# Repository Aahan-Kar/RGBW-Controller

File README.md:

# RGBW LED Strip Controller

Welcome to the repository for the RGBW LED Strip Controller! This project is designed for enthusiasts and professionals looking to control non-addressable RGBW LED strips with precision and flexibility. Using a Teensy 3.2 microcontroller, this controller offers high-frequency PWM for smooth LED dimming, compatibility with both RGB and single-color strips, and both manual and software control options.

## Features

- **High-Frequency PWM**: The controller operates at a 23.4 kHz PWM frequency to minimize visible flicker, ensuring smooth light output.
- **Compatibility**: Designed for use with non-addressable RGBW LED strips, but also supports RGB and single-color (white) strips.
- **12V Input**: Supports a 12V input for LED driving and internal electronics, ensuring wide compatibility with common LED strip specifications.
- **Power Control**: Includes a power on/off switch for easy power management.
- **Manual Control**: Features four knobs for adjusting the brightness levels of the Red, Green, Blue, and White channels independently.
- **USB Connectivity**: Offers USB connectivity for software control, making it suitable for integration with computer-managed setups like 3D printers with Raspberry Pi controllers.
- **Mode Selection**: A rocker switch allows for easy toggling between manual (hardware) control and software control modes.

## Repository Contents

- `Eagle/` - Contains Eagle CAD files including both the electronic schematics and PCB layout designs in a single directory, as preferred by Eagle CAD.
- `Gerber/` - Gerber files ready for PCB fabrication.
- `Code/` - Source code for the Teensy 3.2 microcontroller, including the PWM control and USB communication logic.
- `3DCAD/` - 3D CAD files for the controller's enclosure, suitable for 3D printing.

## Getting Started

### Hardware Setup

1. **Power Supply Connection**: Connect a 12V power supply to the barrel connector. Ensure your power supply can handle the current draw of your LED setup.
2. **Power On**: Use the power switch to turn on the controller.
3. **LED Strip Connection**: Connect your RGBW, RGB, or White LED strip to the appropriate terminals on the controller.

### Manual Control

- With the mode selector switched to hardware control, use the knobs on the controller to adjust the brightness levels of each channel to your liking.

### Software Control

- Ensure the mode selector is set to software control.
- Connect the controller to your computer via USB. It should be recognized as a serial (RS232) device.
- You can now send commands from your computer to adjust the LED strip's settings. This is particularly useful for automated setups like lighting effects for 3D printers.

## Contributing

Contributions to this project are welcome! Whether it's bug fixes, feature enhancements, or documentation improvements, please feel free to fork the repository and submit a pull request.

## License

This project is released under the [MIT License](LICENSE.md). Feel free to use, modify, and distribute the code and designs as per the license terms.

## Contact

For questions, suggestions, or to report issues, please open an issue in this repository, and we'll get back to you as soon as possible.

Happy Lighting!

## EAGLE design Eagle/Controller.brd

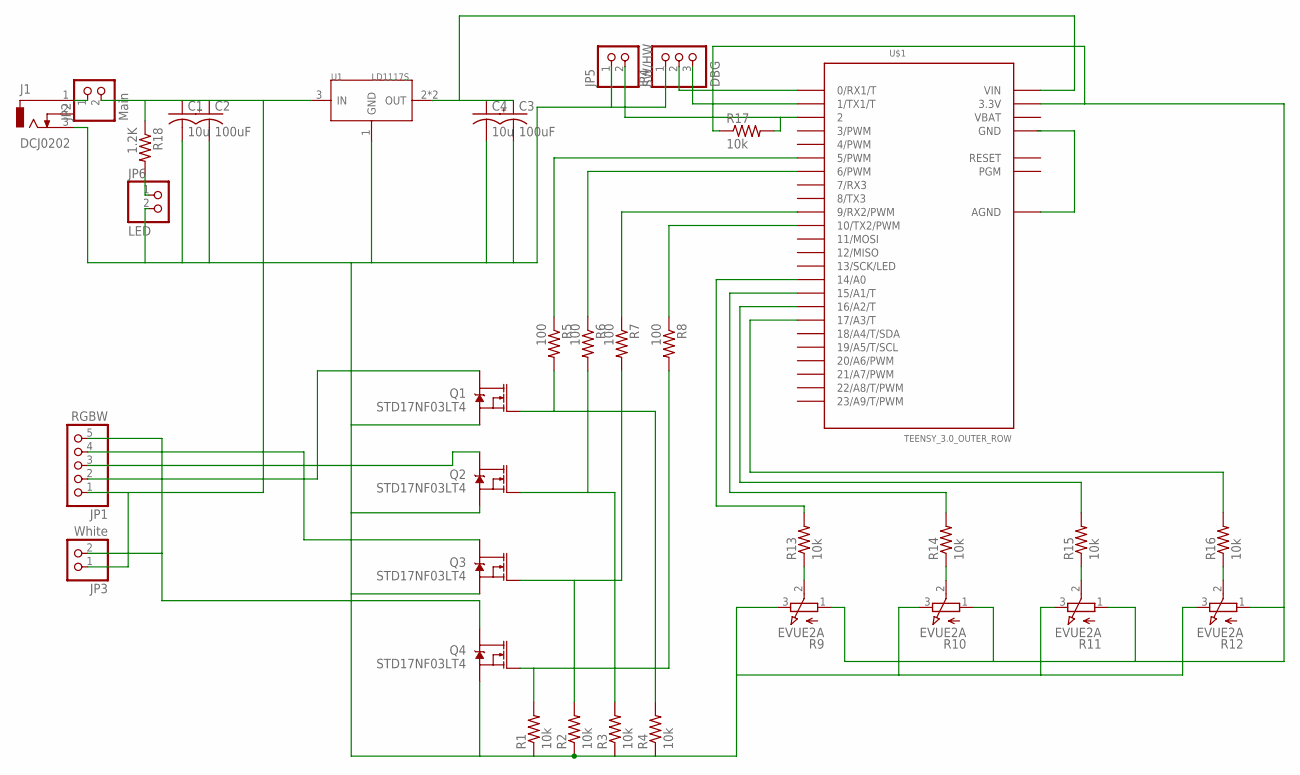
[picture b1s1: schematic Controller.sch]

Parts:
C1, C4: 10u; ADAFRUIT_C0805
C2, C3: 100uF; RCL_TT2D6
J1: DCJ0202
JP1: RGBW; 1X05/90
JP2: Main; 1X02
JP3: White; 1X02/90
JP4: DBG; 1X03/90
JP5: SW/HW; 1X02
JP6: LED; 1X02
Q1, Q2, Q3, Q4: STD17NF03LT4; DPAK
R1, R2, R3, R4, R13, R14, R15, R16, R17: 10k; R0805
R5, R6, R7, R8: 100; R0805
R9, R10, R11, R12: EVUE2A; EVUE
R18: 1.2K; R0805
U1: LD1117S; SOT-223
U$1: TEENSY_3.0_OUTER_ROW; TEENSY_3.0-3.2&LC_OUTER_ROW

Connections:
GND: C1.2, C2.-, C3.-, C4.2, J1.3, JP4.1, JP5.1, JP6.2, Q1.3 (S), Q2.3 (S), Q3.3 (S), Q4.3 (S), R1.1, R2.1, R3.1, R4.1, R9.3 (E), R10.3 (E), R11.3 (E), R12.3 (E), U1.1 (GND), U$1.GND, U$1.GND1 (GND)
unnamed: C1.1, C2.+, JP1.1, JP2.2, JP3.1, R18.1, U1.3 (IN)
unnamed: C3.+, C4.1, U1.2 (OUT), U1.TER (OUT), U$1.VIN
unnamed: R5.1, U$1.5 (5/PWM)
unnamed: Q4.1 (G), R1.2, R8.2
unnamed: Q3.1 (G), R2.2, R7.2
unnamed: Q2.1 (G), R3.2, R6.2
unnamed: Q1.1 (G), R4.2, R5.2
unnamed: R6.1, U$1.6 (6/PWM)
unnamed: R7.1, U$1.9 (9/RX2/PWM)
unnamed: R8.1, U$1.10 (10/TX2/PWM)
unnamed: R9.2 (S), R13.1
unnamed: JP1.2, Q1.4 (D)
unnamed: JP1.3, Q2.4 (D)
unnamed: JP1.4, Q3.4 (D)
unnamed: JP1.5, JP3.2, Q4.4 (D)
unnamed: J1.1, JP2.1
unnamed: R10.2 (S), R14.1
unnamed: R11.2 (S), R15.1
unnamed: R12.2 (S), R16.1
unnamed: R9.1 (A), R10.1 (A), R11.1 (A), R12.1 (A), R17.1, U$1.3.3V, U$1.3.3V1 (3.3V)
unnamed: R13.2, U$1.14/A0
unnamed: R14.2, U$1.15/A1 (15/A1/T)
unnamed: R15.2, U$1.16/A2 (16/A2/T)
unnamed: R16.2, U$1.17/A3 (17/A3/T)
unnamed: JP5.2, R17.2, U$1.2
unnamed: JP4.2, U$1.0 (0/RX1/T)
unnamed: JP4.3, U$1.1 (1/TX1/T)
unnamed: JP6.1, R18.2
VBAT: U$1.VBAT

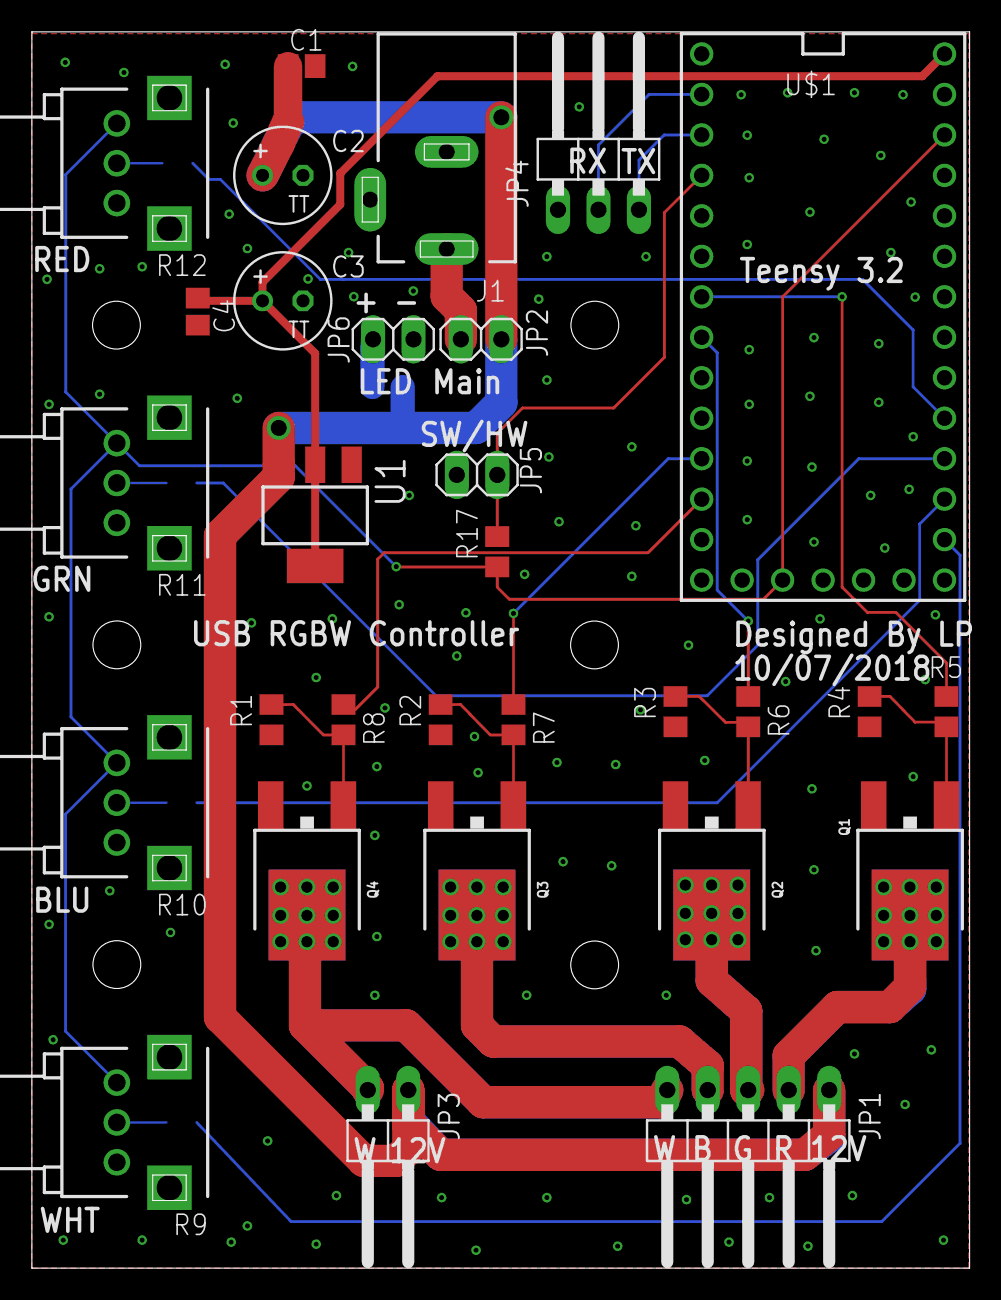
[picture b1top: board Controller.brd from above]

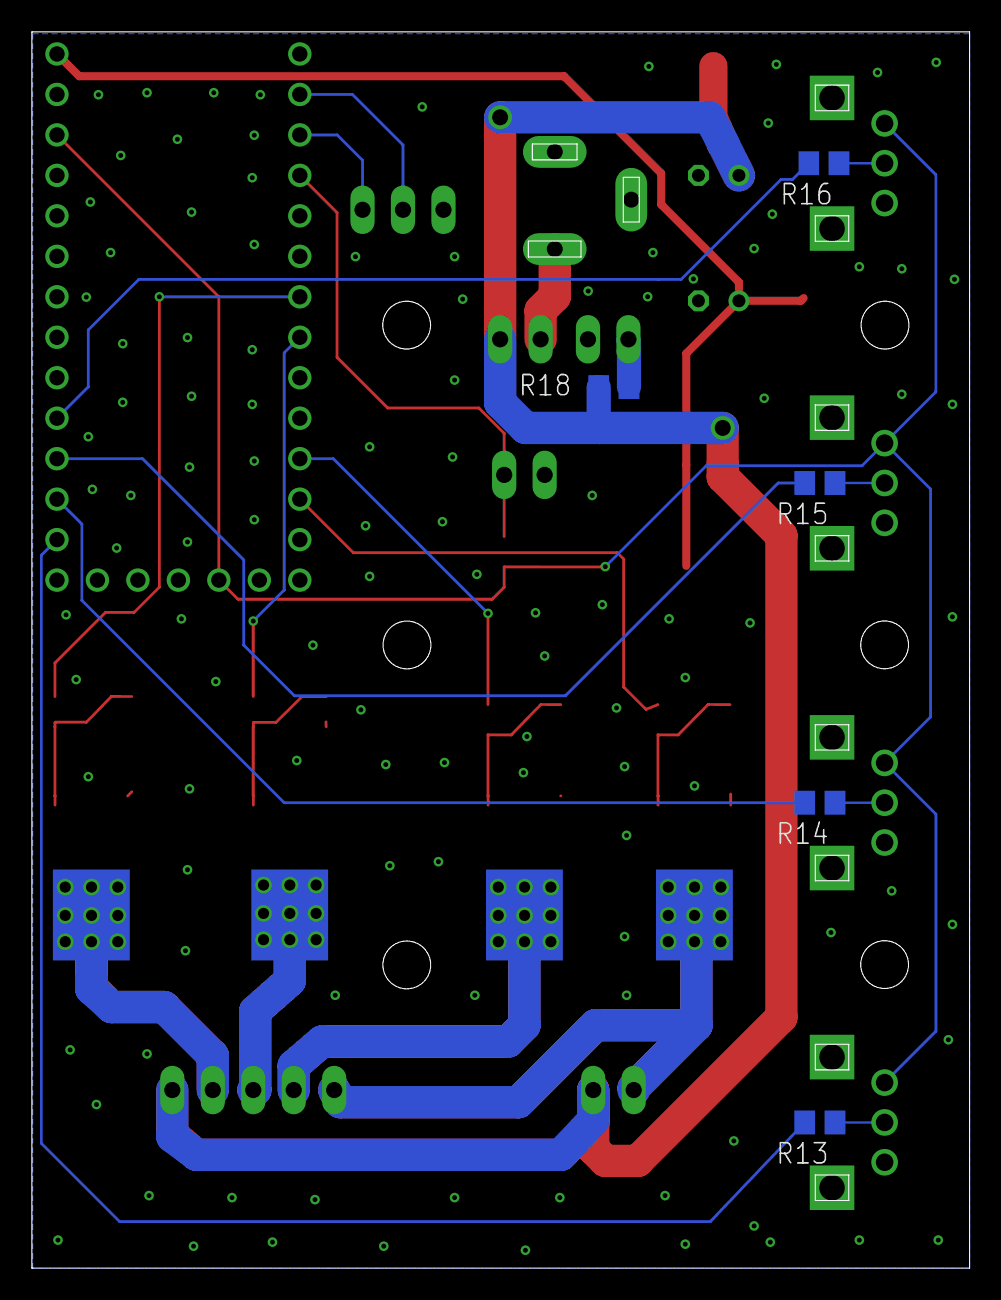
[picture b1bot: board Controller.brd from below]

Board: 2 copper layers, 58.9 x 77.6 mm, 35 parts (5 on the bottom side), 29 nets.

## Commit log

2024-02-09 Initial release

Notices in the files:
parts and their libraries:
SparkFun-DiscreteSemi: Licensing: Creative Commons ShareAlike 4.0 International - https://creativecommons.org/licenses/by-sa/4.0
